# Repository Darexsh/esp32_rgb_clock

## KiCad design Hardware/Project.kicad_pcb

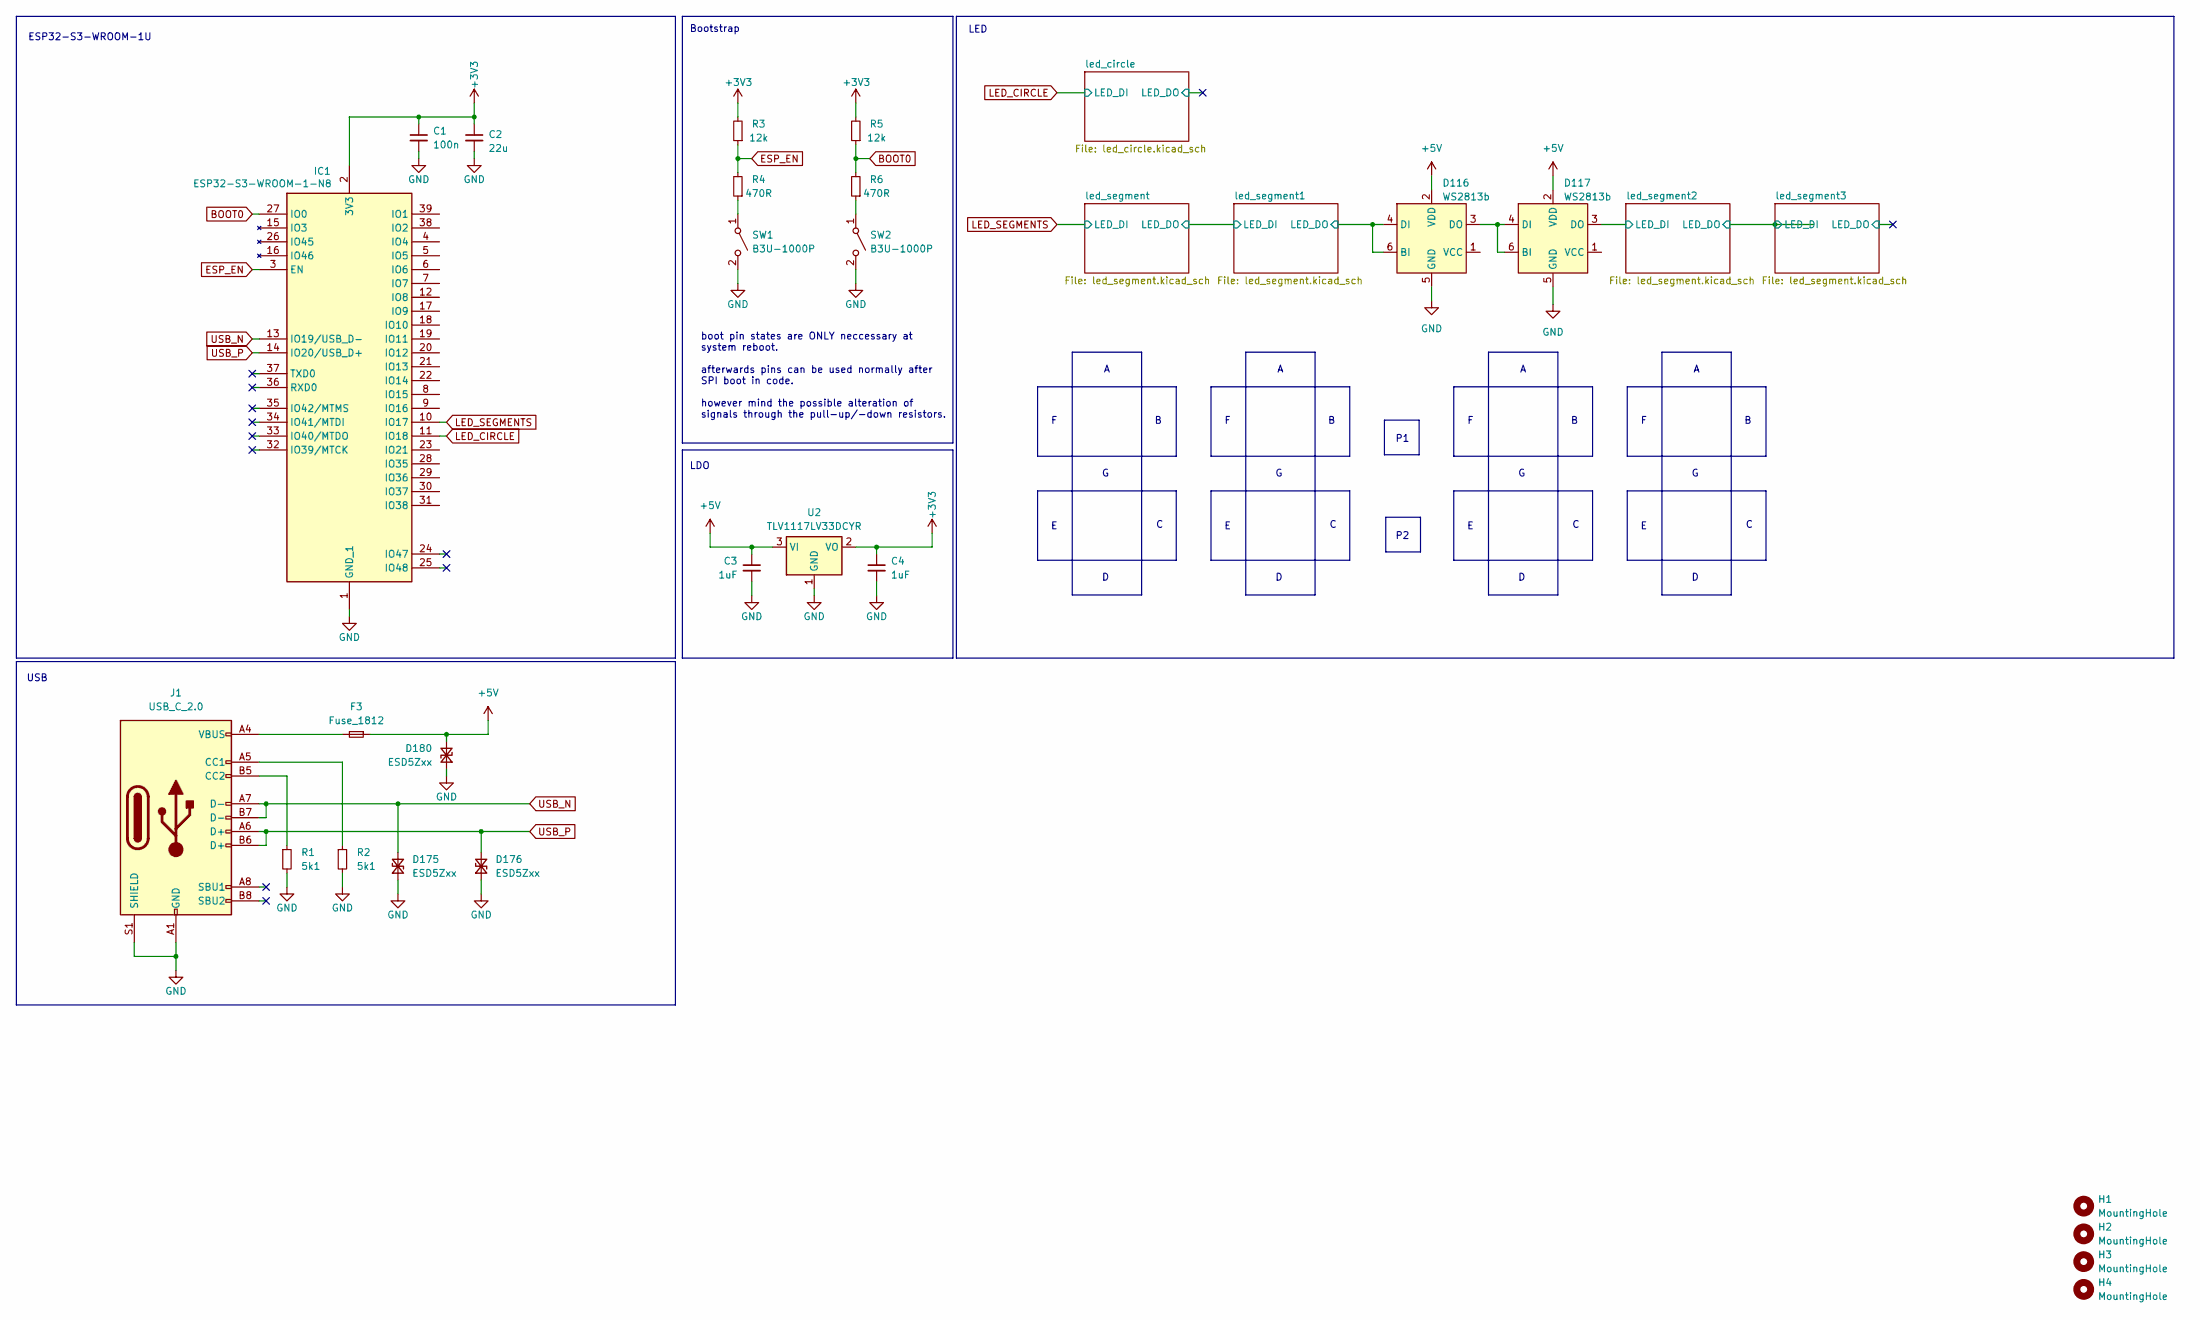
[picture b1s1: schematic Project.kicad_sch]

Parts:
C1: 100n; C_0603_1608Metric
C2: 22u; C_0603_1608Metric
C3, C4: 1uF; C_0603_1608Metric
D116, D117: WS2813b; LED_WS2812_PLCC6_5.0x5.0mm_P1.6mm
D175, D176, D180: ESD5Zxx; D_SOD-523
F3: Fuse_1812; Fuse_1812_4532Metric
H1, H2, H3, H4: MountingHole; MountingHole_3.2mm_M3
IC1: ESP32-S3-WROOM-1-N8; ESP32S3WROOM1N8R8
J1: USB_C_2.0; USB-C
R1, R2: 5k1; R_0603_1608Metric
R3, R5: 12k; R_0603_1608Metric
R4, R6: 470R; R_0603_1608Metric
SW1, SW2: B3U-1000P
U2: TLV1117LV33DCYR; SOT-223-3_TabPin2

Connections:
+3V3: C1.1, C2.1, C4.1, IC1.2 (3V3), R3.2, R5.2, U2.2 (VO)
+5V: C3.1, D116.2 (VDD), D117.2 (VDD), D180.2 (A2), F3.1, U2.3 (VI); also elsewhere on the board
/led_segment1/LED_DO: D116.4 (DI), D116.6 (BI); also elsewhere on the board
/led_segment2/LED_DI: D117.3 (DO); also elsewhere on the board
BOOT0: IC1.27 (IO0), R5.1, R6.2
ESP_EN: IC1.3 (EN), R3.1, R4.2
GND: C1.2, C2.2, C3.2, C4.2, D116.5 (GND), D117.5 (GND), D175.1 (A1), D176.1 (A1), D180.1 (A1), IC1.1 (GND_1), IC1.40 (GND_2), IC1.41 (GND_3), IC1.42 (GND_4), IC1.43 (GND_5), IC1.44 (GND_6), IC1.45 (GND_7), IC1.46 (GND_8), IC1.47 (GND_9), IC1.48 (GND_10), IC1.49 (GND_11), J1.A1 (GND), J1.A12 (GND), J1.S1 (SHIELD), R1.2, R2.2, SW1.2 (B), SW2.2 (B), U2.1 (GND); also elsewhere on the board
LED_CIRCLE: IC1.11 (IO18); also elsewhere on the board
LED_SEGMENTS: IC1.10 (IO17); also elsewhere on the board
unnamed: D116.3 (DO), D117.4 (DI), D117.6 (BI)
unnamed: F3.2, J1.A4 (VBUS), J1.A9 (VBUS)
unnamed: J1.A5 (CC1), R2.1
unnamed: J1.B5 (CC2), R1.1
unnamed: R4.1, SW1.1 (A)
unnamed: R6.1, SW2.1 (A)
USB_N: D175.2 (A2), IC1.13 (IO19/USB_D-), J1.A7 (D-), J1.B7 (D-)
USB_P: D176.2 (A2), IC1.14 (IO20/USB_D+), J1.A6 (D+), J1.B6 (D+)

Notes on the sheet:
LED
USB
LDO
Bootstrap
ESP32-S3-WROOM-1U
boot pin states are ONLY neccessary at system reboot. afterwards pins can be used normally after SPI boot in code. however mind the possible alteration of signals through the pull-up/-down resistors.

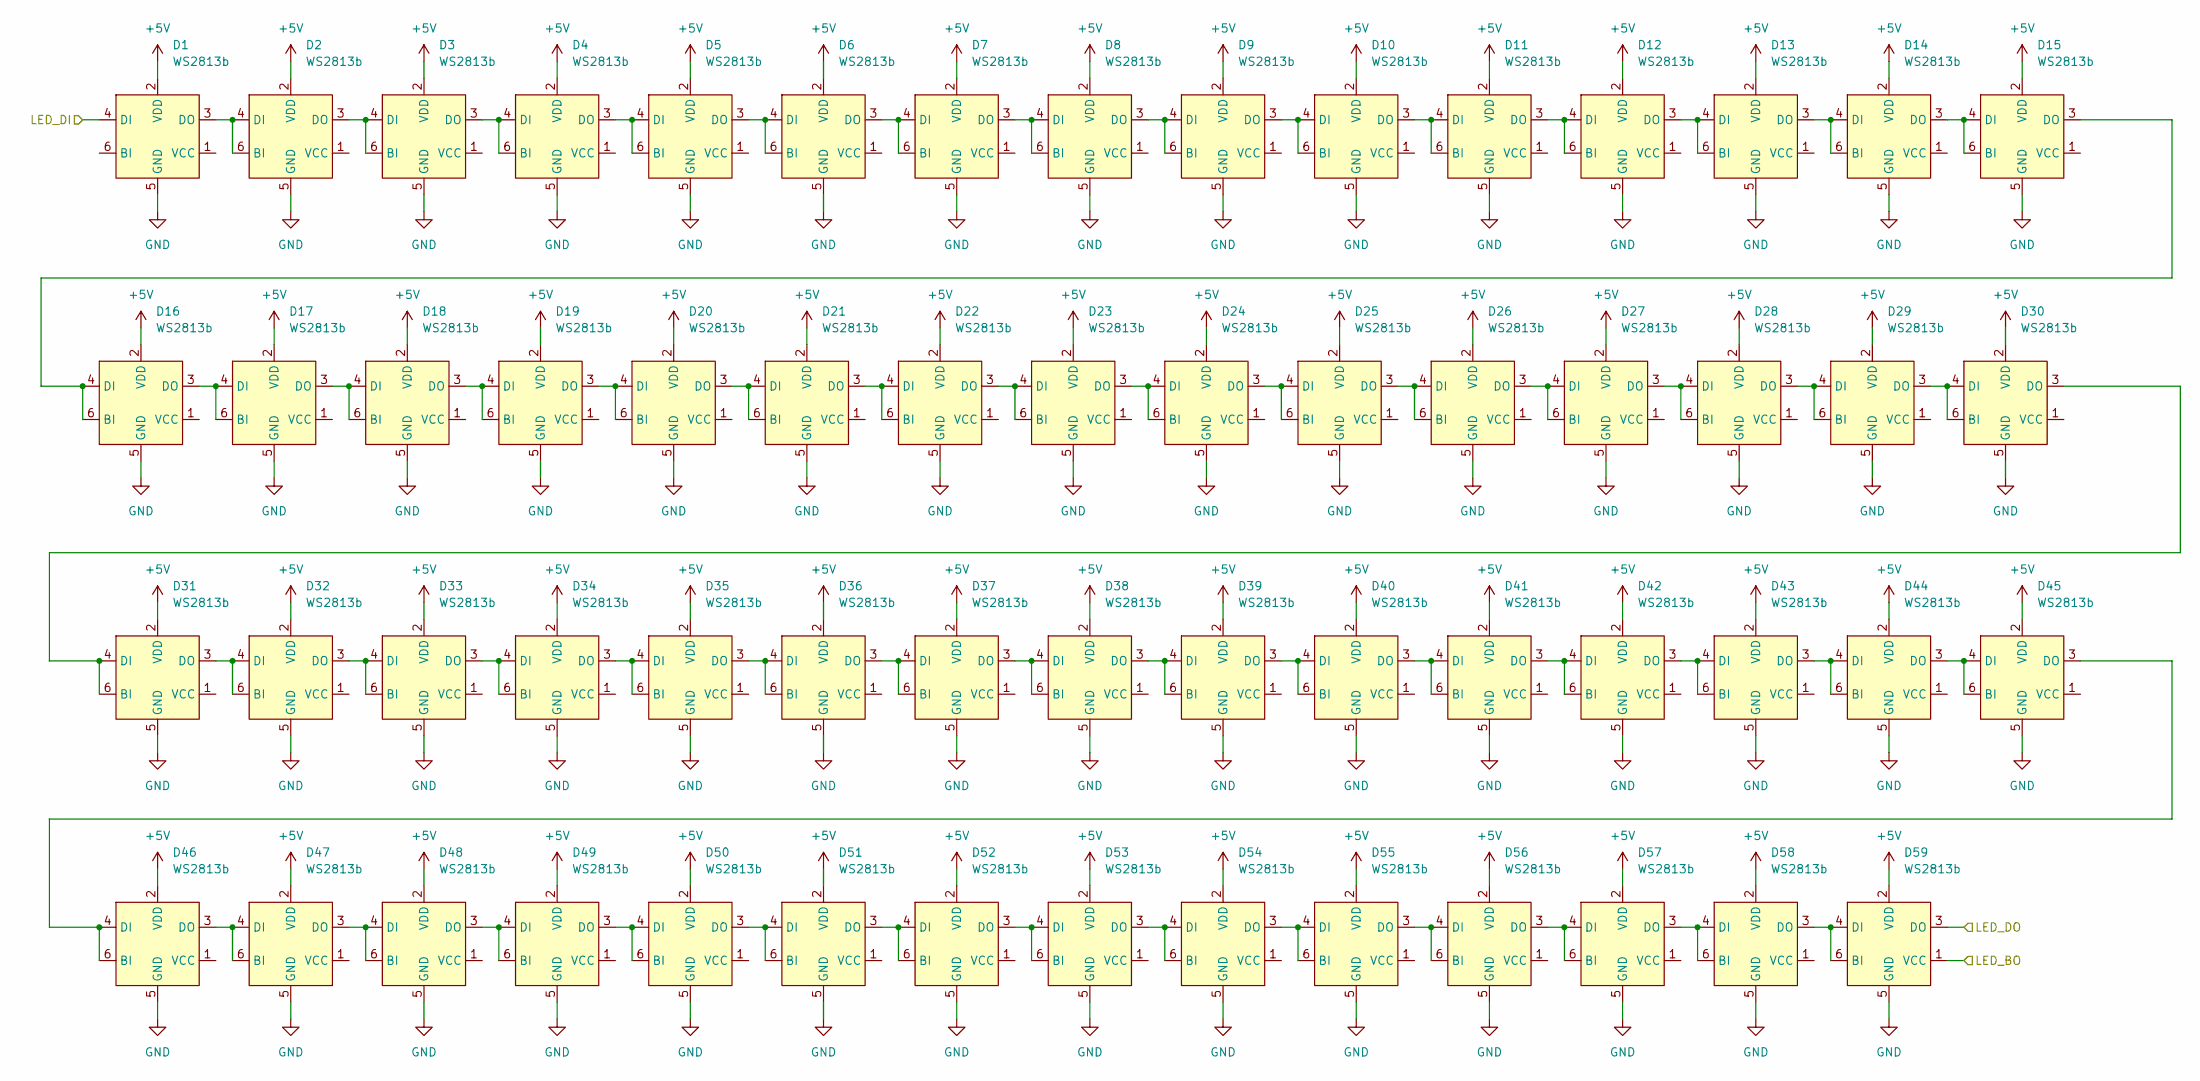
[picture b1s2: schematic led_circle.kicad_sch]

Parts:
D1, D2, D3, D4, D5, D6, D7, D8, D9, D10, D11, D12, D13, D14, D15, D16, D17, D18, D19, D20, D21, D22, D23, D24, D25, D26, D27, D28, D29, D30, D31, D32, D33, D34, D35, D36, D37, D38, D39, D40, D41, D42, D43, D44, D45, D46, D47, D48, D49, D50, D51, D52, D53, D54, D55, D56, D57, D58, D59: WS2813b; LED_WS2812_PLCC6_5.0x5.0mm_P1.6mm

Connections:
+5V: D1.2 (VDD), D2.2 (VDD), D3.2 (VDD), D4.2 (VDD), D5.2 (VDD), D6.2 (VDD), D7.2 (VDD), D8.2 (VDD), D9.2 (VDD), D10.2 (VDD), D11.2 (VDD), D12.2 (VDD), D13.2 (VDD), D14.2 (VDD), D15.2 (VDD), D16.2 (VDD), D17.2 (VDD), D18.2 (VDD), D19.2 (VDD), D20.2 (VDD), D21.2 (VDD), D22.2 (VDD), D23.2 (VDD), D24.2 (VDD), D25.2 (VDD), D26.2 (VDD), D27.2 (VDD), D28.2 (VDD), D29.2 (VDD), D30.2 (VDD), D31.2 (VDD), D32.2 (VDD), D33.2 (VDD), D34.2 (VDD), D35.2 (VDD), D36.2 (VDD), D37.2 (VDD), D38.2 (VDD), D39.2 (VDD), D40.2 (VDD), D41.2 (VDD), D42.2 (VDD), D43.2 (VDD), D44.2 (VDD), D45.2 (VDD), D46.2 (VDD), D47.2 (VDD), D48.2 (VDD), D49.2 (VDD), D50.2 (VDD), D51.2 (VDD), D52.2 (VDD), D53.2 (VDD), D54.2 (VDD), D55.2 (VDD), D56.2 (VDD), D57.2 (VDD), D58.2 (VDD), D59.2 (VDD); also elsewhere on the board
/led_circle/LED_BO: D59.1 (VCC)
/led_circle/LED_DO: D59.3 (DO)
GND: D1.5 (GND), D2.5 (GND), D3.5 (GND), D4.5 (GND), D5.5 (GND), D6.5 (GND), D7.5 (GND), D8.5 (GND), D9.5 (GND), D10.5 (GND), D11.5 (GND), D12.5 (GND), D13.5 (GND), D14.5 (GND), D15.5 (GND), D16.5 (GND), D17.5 (GND), D18.5 (GND), D19.5 (GND), D20.5 (GND), D21.5 (GND), D22.5 (GND), D23.5 (GND), D24.5 (GND), D25.5 (GND), D26.5 (GND), D27.5 (GND), D28.5 (GND), D29.5 (GND), D30.5 (GND), D31.5 (GND), D32.5 (GND), D33.5 (GND), D34.5 (GND), D35.5 (GND), D36.5 (GND), D37.5 (GND), D38.5 (GND), D39.5 (GND), D40.5 (GND), D41.5 (GND), D42.5 (GND), D43.5 (GND), D44.5 (GND), D45.5 (GND), D46.5 (GND), D47.5 (GND), D48.5 (GND), D49.5 (GND), D50.5 (GND), D51.5 (GND), D52.5 (GND), D53.5 (GND), D54.5 (GND), D55.5 (GND), D56.5 (GND), D57.5 (GND), D58.5 (GND), D59.5 (GND); also elsewhere on the board
LED_CIRCLE: D1.4 (DI); also elsewhere on the board
unnamed: D1.3 (DO), D2.4 (DI), D2.6 (BI)
unnamed: D2.3 (DO), D3.4 (DI), D3.6 (BI)
unnamed: D3.3 (DO), D4.4 (DI), D4.6 (BI)
unnamed: D4.3 (DO), D5.4 (DI), D5.6 (BI)
unnamed: D5.3 (DO), D6.4 (DI), D6.6 (BI)
unnamed: D6.3 (DO), D7.4 (DI), D7.6 (BI)
unnamed: D7.3 (DO), D8.4 (DI), D8.6 (BI)
unnamed: D8.3 (DO), D9.4 (DI), D9.6 (BI)
unnamed: D9.3 (DO), D10.4 (DI), D10.6 (BI)
unnamed: D10.3 (DO), D11.4 (DI), D11.6 (BI)
unnamed: D11.3 (DO), D12.4 (DI), D12.6 (BI)
unnamed: D12.3 (DO), D13.4 (DI), D13.6 (BI)
unnamed: D13.3 (DO), D14.4 (DI), D14.6 (BI)
unnamed: D14.3 (DO), D15.4 (DI), D15.6 (BI)
unnamed: D15.3 (DO), D16.4 (DI), D16.6 (BI)
unnamed: D16.3 (DO), D17.4 (DI), D17.6 (BI)
unnamed: D17.3 (DO), D18.4 (DI), D18.6 (BI)
unnamed: D18.3 (DO), D19.4 (DI), D19.6 (BI)
unnamed: D19.3 (DO), D20.4 (DI), D20.6 (BI)
unnamed: D20.3 (DO), D21.4 (DI), D21.6 (BI)
unnamed: D21.3 (DO), D22.4 (DI), D22.6 (BI)
unnamed: D22.3 (DO), D23.4 (DI), D23.6 (BI)
unnamed: D23.3 (DO), D24.4 (DI), D24.6 (BI)
unnamed: D24.3 (DO), D25.4 (DI), D25.6 (BI)
unnamed: D25.3 (DO), D26.4 (DI), D26.6 (BI)
unnamed: D26.3 (DO), D27.4 (DI), D27.6 (BI)
unnamed: D27.3 (DO), D28.4 (DI), D28.6 (BI)
unnamed: D28.3 (DO), D29.4 (DI), D29.6 (BI)
unnamed: D29.3 (DO), D30.4 (DI), D30.6 (BI)
unnamed: D30.3 (DO), D31.4 (DI), D31.6 (BI)
unnamed: D31.3 (DO), D32.4 (DI), D32.6 (BI)
unnamed: D32.3 (DO), D33.4 (DI), D33.6 (BI)
unnamed: D33.3 (DO), D34.4 (DI), D34.6 (BI)
unnamed: D34.3 (DO), D35.4 (DI), D35.6 (BI)
unnamed: D35.3 (DO), D36.4 (DI), D36.6 (BI)
unnamed: D36.3 (DO), D37.4 (DI), D37.6 (BI)
unnamed: D37.3 (DO), D38.4 (DI), D38.6 (BI)
unnamed: D38.3 (DO), D39.4 (DI), D39.6 (BI)
unnamed: D39.3 (DO), D40.4 (DI), D40.6 (BI)
unnamed: D40.3 (DO), D41.4 (DI), D41.6 (BI)
unnamed: D41.3 (DO), D42.4 (DI), D42.6 (BI)
unnamed: D42.3 (DO), D43.4 (DI), D43.6 (BI)
unnamed: D43.3 (DO), D44.4 (DI), D44.6 (BI)
unnamed: D44.3 (DO), D45.4 (DI), D45.6 (BI)
unnamed: D45.3 (DO), D46.4 (DI), D46.6 (BI)
unnamed: D46.3 (DO), D47.4 (DI), D47.6 (BI)
unnamed: D47.3 (DO), D48.4 (DI), D48.6 (BI)
unnamed: D48.3 (DO), D49.4 (DI), D49.6 (BI)
unnamed: D49.3 (DO), D50.4 (DI), D50.6 (BI)
unnamed: D50.3 (DO), D51.4 (DI), D51.6 (BI)
unnamed: D51.3 (DO), D52.4 (DI), D52.6 (BI)
unnamed: D52.3 (DO), D53.4 (DI), D53.6 (BI)
unnamed: D53.3 (DO), D54.4 (DI), D54.6 (BI)
unnamed: D54.3 (DO), D55.4 (DI), D55.6 (BI)
unnamed: D55.3 (DO), D56.4 (DI), D56.6 (BI)
unnamed: D56.3 (DO), D57.4 (DI), D57.6 (BI)
unnamed: D57.3 (DO), D58.4 (DI), D58.6 (BI)
unnamed: D58.3 (DO), D59.4 (DI), D59.6 (BI)

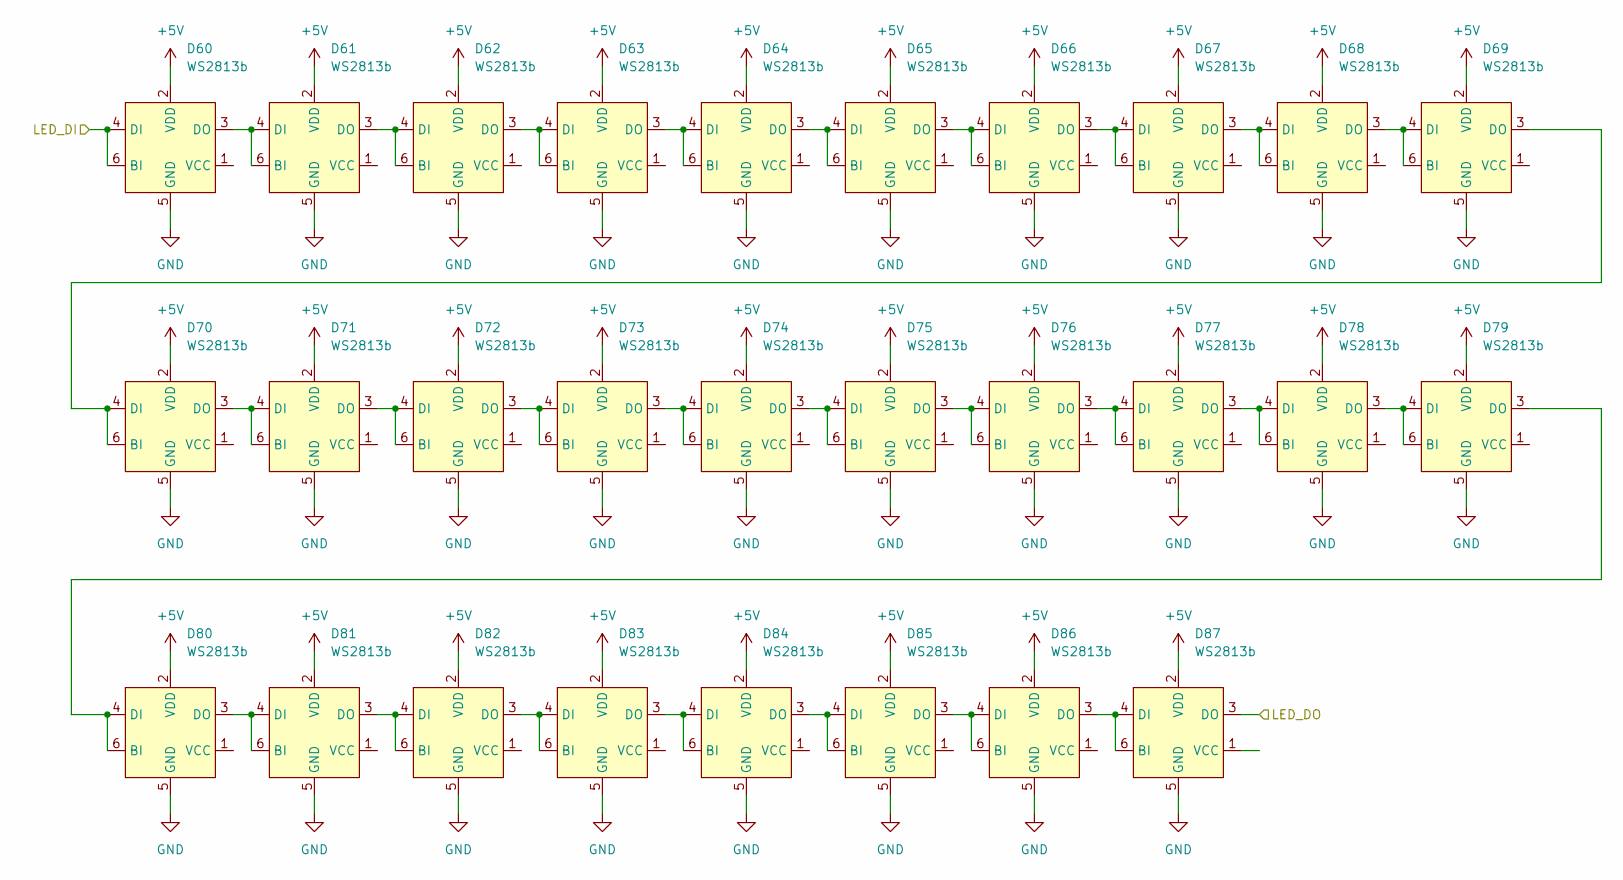
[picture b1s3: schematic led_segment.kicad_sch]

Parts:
D60, D61, D62, D63, D64, D65, D66, D67, D68, D69, D70, D71, D72, D73, D74, D75, D76, D77, D78, D79, D80, D81, D82, D83, D84, D85, D86, D87: WS2813b; LED_WS2812_PLCC6_5.0x5.0mm_P1.6mm

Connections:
+5V: D60.2 (VDD), D61.2 (VDD), D62.2 (VDD), D63.2 (VDD), D64.2 (VDD), D65.2 (VDD), D66.2 (VDD), D67.2 (VDD), D68.2 (VDD), D69.2 (VDD), D70.2 (VDD), D71.2 (VDD), D72.2 (VDD), D73.2 (VDD), D74.2 (VDD), D75.2 (VDD), D76.2 (VDD), D77.2 (VDD), D78.2 (VDD), D79.2 (VDD), D80.2 (VDD), D81.2 (VDD), D82.2 (VDD), D83.2 (VDD), D84.2 (VDD), D85.2 (VDD), D86.2 (VDD), D87.2 (VDD); also elsewhere on the board
/led_segment/LED_DO: D87.3 (DO); also elsewhere on the board
GND: D60.5 (GND), D61.5 (GND), D62.5 (GND), D63.5 (GND), D64.5 (GND), D65.5 (GND), D66.5 (GND), D67.5 (GND), D68.5 (GND), D69.5 (GND), D70.5 (GND), D71.5 (GND), D72.5 (GND), D73.5 (GND), D74.5 (GND), D75.5 (GND), D76.5 (GND), D77.5 (GND), D78.5 (GND), D79.5 (GND), D80.5 (GND), D81.5 (GND), D82.5 (GND), D83.5 (GND), D84.5 (GND), D85.5 (GND), D86.5 (GND), D87.5 (GND); also elsewhere on the board
LED_SEGMENTS: D60.4 (DI), D60.6 (BI); also elsewhere on the board
unnamed: D60.3 (DO), D61.4 (DI), D61.6 (BI)
unnamed: D61.3 (DO), D62.4 (DI), D62.6 (BI)
unnamed: D62.3 (DO), D63.4 (DI), D63.6 (BI)
unnamed: D63.3 (DO), D64.4 (DI), D64.6 (BI)
unnamed: D64.3 (DO), D65.4 (DI), D65.6 (BI)
unnamed: D65.3 (DO), D66.4 (DI), D66.6 (BI)
unnamed: D66.3 (DO), D67.4 (DI), D67.6 (BI)
unnamed: D67.3 (DO), D68.4 (DI), D68.6 (BI)
unnamed: D68.3 (DO), D69.4 (DI), D69.6 (BI)
unnamed: D69.3 (DO), D70.4 (DI), D70.6 (BI)
unnamed: D70.3 (DO), D71.4 (DI), D71.6 (BI)
unnamed: D71.3 (DO), D72.4 (DI), D72.6 (BI)
unnamed: D72.3 (DO), D73.4 (DI), D73.6 (BI)
unnamed: D73.3 (DO), D74.4 (DI), D74.6 (BI)
unnamed: D74.3 (DO), D75.4 (DI), D75.6 (BI)
unnamed: D75.3 (DO), D76.4 (DI), D76.6 (BI)
unnamed: D76.3 (DO), D77.4 (DI), D77.6 (BI)
unnamed: D77.3 (DO), D78.4 (DI), D78.6 (BI)
unnamed: D78.3 (DO), D79.4 (DI), D79.6 (BI)
unnamed: D79.3 (DO), D80.4 (DI), D80.6 (BI)
unnamed: D80.3 (DO), D81.4 (DI), D81.6 (BI)
unnamed: D81.3 (DO), D82.4 (DI), D82.6 (BI)
unnamed: D82.3 (DO), D83.4 (DI), D83.6 (BI)
unnamed: D83.3 (DO), D84.4 (DI), D84.6 (BI)
unnamed: D84.3 (DO), D85.4 (DI), D85.6 (BI)
unnamed: D85.3 (DO), D86.4 (DI), D86.6 (BI)
unnamed: D86.3 (DO), D87.4 (DI), D87.6 (BI)

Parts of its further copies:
D88, D89, D90, D91, D92, D93, D94, D95, D96, D97, D98, D99, D100, D101, D102, D103, D104, D105, D106, D107, D108, D109, D110, D111, D112, D113, D114, D115, D118, D119, D120, D121, D122, D123, D124, D125, D126, D127, D128, D129, D130, D131, D132, D133, D134, D135, D136, D137, D138, D139, D140, D141, D142, D143, D144, D145, D146, D147, D148, D149, D150, D151, D152, D153, D154, D155, D156, D157, D158, D159, D160, D161, D162, D163, D164, D165, D166, D167, D168, D169, D170, D171, D172, D173: WS2813b; LED_WS2812_PLCC6_5.0x5.0mm_P1.6mm

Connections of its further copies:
+5V: D88.2 (VDD), D89.2 (VDD), D90.2 (VDD), D91.2 (VDD), D92.2 (VDD), D93.2 (VDD), D94.2 (VDD), D95.2 (VDD), D96.2 (VDD), D97.2 (VDD), D98.2 (VDD), D99.2 (VDD), D100.2 (VDD), D101.2 (VDD), D102.2 (VDD), D103.2 (VDD), D104.2 (VDD), D105.2 (VDD), D106.2 (VDD), D107.2 (VDD), D108.2 (VDD), D109.2 (VDD), D110.2 (VDD), D111.2 (VDD), D112.2 (VDD), D113.2 (VDD), D114.2 (VDD), D115.2 (VDD), D118.2 (VDD), D119.2 (VDD), D120.2 (VDD), D121.2 (VDD), D122.2 (VDD), D123.2 (VDD), D124.2 (VDD), D125.2 (VDD), D126.2 (VDD), D127.2 (VDD), D128.2 (VDD), D129.2 (VDD), D130.2 (VDD), D131.2 (VDD), D132.2 (VDD), D133.2 (VDD), D134.2 (VDD), D135.2 (VDD), D136.2 (VDD), D137.2 (VDD), D138.2 (VDD), D139.2 (VDD), D140.2 (VDD), D141.2 (VDD), D142.2 (VDD), D143.2 (VDD), D144.2 (VDD), D145.2 (VDD), D146.2 (VDD), D147.2 (VDD), D148.2 (VDD), D149.2 (VDD), D150.2 (VDD), D151.2 (VDD), D152.2 (VDD), D153.2 (VDD), D154.2 (VDD), D155.2 (VDD), D156.2 (VDD), D157.2 (VDD), D158.2 (VDD), D159.2 (VDD), D160.2 (VDD), D161.2 (VDD), D162.2 (VDD), D163.2 (VDD), D164.2 (VDD), D165.2 (VDD), D166.2 (VDD), D167.2 (VDD), D168.2 (VDD), D169.2 (VDD), D170.2 (VDD), D171.2 (VDD), D172.2 (VDD), D173.2 (VDD); also elsewhere on the board
/led_segment1/LED_DO: D115.3 (DO); also elsewhere on the board
/led_segment2/LED_DI: D118.4 (DI), D118.6 (BI); also elsewhere on the board
/led_segment2/LED_DO: D145.3 (DO), D146.4 (DI), D146.6 (BI)
/led_segment3/LED_DO: D173.3 (DO)
/led_segment/LED_DO: D88.4 (DI), D88.6 (BI); also elsewhere on the board
GND: D88.5 (GND), D89.5 (GND), D90.5 (GND), D91.5 (GND), D92.5 (GND), D93.5 (GND), D94.5 (GND), D95.5 (GND), D96.5 (GND), D97.5 (GND), D98.5 (GND), D99.5 (GND), D100.5 (GND), D101.5 (GND), D102.5 (GND), D103.5 (GND), D104.5 (GND), D105.5 (GND), D106.5 (GND), D107.5 (GND), D108.5 (GND), D109.5 (GND), D110.5 (GND), D111.5 (GND), D112.5 (GND), D113.5 (GND), D114.5 (GND), D115.5 (GND), D118.5 (GND), D119.5 (GND), D120.5 (GND), D121.5 (GND), D122.5 (GND), D123.5 (GND), D124.5 (GND), D125.5 (GND), D126.5 (GND), D127.5 (GND), D128.5 (GND), D129.5 (GND), D130.5 (GND), D131.5 (GND), D132.5 (GND), D133.5 (GND), D134.5 (GND), D135.5 (GND), D136.5 (GND), D137.5 (GND), D138.5 (GND), D139.5 (GND), D140.5 (GND), D141.5 (GND), D142.5 (GND), D143.5 (GND), D144.5 (GND), D145.5 (GND), D146.5 (GND), D147.5 (GND), D148.5 (GND), D149.5 (GND), D150.5 (GND), D151.5 (GND), D152.5 (GND), D153.5 (GND), D154.5 (GND), D155.5 (GND), D156.5 (GND), D157.5 (GND), D158.5 (GND), D159.5 (GND), D160.5 (GND), D161.5 (GND), D162.5 (GND), D163.5 (GND), D164.5 (GND), D165.5 (GND), D166.5 (GND), D167.5 (GND), D168.5 (GND), D169.5 (GND), D170.5 (GND), D171.5 (GND), D172.5 (GND), D173.5 (GND); also elsewhere on the board
unnamed: D88.3 (DO), D89.4 (DI), D89.6 (BI)
unnamed: D89.3 (DO), D90.4 (DI), D90.6 (BI)
unnamed: D90.3 (DO), D91.4 (DI), D91.6 (BI)
unnamed: D91.3 (DO), D92.4 (DI), D92.6 (BI)
unnamed: D92.3 (DO), D93.4 (DI), D93.6 (BI)
unnamed: D93.3 (DO), D94.4 (DI), D94.6 (BI)
unnamed: D94.3 (DO), D95.4 (DI), D95.6 (BI)
unnamed: D95.3 (DO), D96.4 (DI), D96.6 (BI)
unnamed: D96.3 (DO), D97.4 (DI), D97.6 (BI)
unnamed: D97.3 (DO), D98.4 (DI), D98.6 (BI)
unnamed: D98.3 (DO), D99.4 (DI), D99.6 (BI)
unnamed: D99.3 (DO), D100.4 (DI), D100.6 (BI)
unnamed: D100.3 (DO), D101.4 (DI), D101.6 (BI)
unnamed: D101.3 (DO), D102.4 (DI), D102.6 (BI)
unnamed: D102.3 (DO), D103.4 (DI), D103.6 (BI)
unnamed: D103.3 (DO), D104.4 (DI), D104.6 (BI)
unnamed: D104.3 (DO), D105.4 (DI), D105.6 (BI)
unnamed: D105.3 (DO), D106.4 (DI), D106.6 (BI)
unnamed: D106.3 (DO), D107.4 (DI), D107.6 (BI)
unnamed: D107.3 (DO), D108.4 (DI), D108.6 (BI)
unnamed: D108.3 (DO), D109.4 (DI), D109.6 (BI)
unnamed: D109.3 (DO), D110.4 (DI), D110.6 (BI)
unnamed: D110.3 (DO), D111.4 (DI), D111.6 (BI)
unnamed: D111.3 (DO), D112.4 (DI), D112.6 (BI)
unnamed: D112.3 (DO), D113.4 (DI), D113.6 (BI)
unnamed: D113.3 (DO), D114.4 (DI), D114.6 (BI)
unnamed: D114.3 (DO), D115.4 (DI), D115.6 (BI)
unnamed: D118.3 (DO), D119.4 (DI), D119.6 (BI)
unnamed: D119.3 (DO), D120.4 (DI), D120.6 (BI)
unnamed: D120.3 (DO), D121.4 (DI), D121.6 (BI)
unnamed: D121.3 (DO), D122.4 (DI), D122.6 (BI)
unnamed: D122.3 (DO), D123.4 (DI), D123.6 (BI)
unnamed: D123.3 (DO), D124.4 (DI), D124.6 (BI)
unnamed: D124.3 (DO), D125.4 (DI), D125.6 (BI)
unnamed: D125.3 (DO), D126.4 (DI), D126.6 (BI)
unnamed: D126.3 (DO), D127.4 (DI), D127.6 (BI)
unnamed: D127.3 (DO), D128.4 (DI), D128.6 (BI)
unnamed: D128.3 (DO), D129.4 (DI), D129.6 (BI)
unnamed: D129.3 (DO), D130.4 (DI), D130.6 (BI)
unnamed: D130.3 (DO), D131.4 (DI), D131.6 (BI)
unnamed: D131.3 (DO), D132.4 (DI), D132.6 (BI)
unnamed: D132.3 (DO), D133.4 (DI), D133.6 (BI)
unnamed: D133.3 (DO), D134.4 (DI), D134.6 (BI)
unnamed: D134.3 (DO), D135.4 (DI), D135.6 (BI)
unnamed: D135.3 (DO), D136.4 (DI), D136.6 (BI)
unnamed: D136.3 (DO), D137.4 (DI), D137.6 (BI)
unnamed: D137.3 (DO), D138.4 (DI), D138.6 (BI)
unnamed: D138.3 (DO), D139.4 (DI), D139.6 (BI)
unnamed: D139.3 (DO), D140.4 (DI), D140.6 (BI)
unnamed: D140.3 (DO), D141.4 (DI), D141.6 (BI)
unnamed: D141.3 (DO), D142.4 (DI), D142.6 (BI)
unnamed: D142.3 (DO), D143.4 (DI), D143.6 (BI)
unnamed: D143.3 (DO), D144.4 (DI), D144.6 (BI)
unnamed: D144.3 (DO), D145.4 (DI), D145.6 (BI)
unnamed: D146.3 (DO), D147.4 (DI), D147.6 (BI)
unnamed: D147.3 (DO), D148.4 (DI), D148.6 (BI)
unnamed: D148.3 (DO), D149.4 (DI), D149.6 (BI)
unnamed: D149.3 (DO), D150.4 (DI), D150.6 (BI)
unnamed: D150.3 (DO), D151.4 (DI), D151.6 (BI)
unnamed: D151.3 (DO), D152.4 (DI), D152.6 (BI)
unnamed: D152.3 (DO), D153.4 (DI), D153.6 (BI)
unnamed: D153.3 (DO), D154.4 (DI), D154.6 (BI)
unnamed: D154.3 (DO), D155.4 (DI), D155.6 (BI)
unnamed: D155.3 (DO), D156.4 (DI), D156.6 (BI)
unnamed: D156.3 (DO), D157.4 (DI), D157.6 (BI)
unnamed: D157.3 (DO), D158.4 (DI), D158.6 (BI)
unnamed: D158.3 (DO), D159.4 (DI), D159.6 (BI)
unnamed: D159.3 (DO), D160.4 (DI), D160.6 (BI)
unnamed: D160.3 (DO), D161.4 (DI), D161.6 (BI)
unnamed: D161.3 (DO), D162.4 (DI), D162.6 (BI)
unnamed: D162.3 (DO), D163.4 (DI), D163.6 (BI)
unnamed: D163.3 (DO), D164.4 (DI), D164.6 (BI)
unnamed: D164.3 (DO), D165.4 (DI), D165.6 (BI)
unnamed: D165.3 (DO), D166.4 (DI), D166.6 (BI)
unnamed: D166.3 (DO), D167.4 (DI), D167.6 (BI)
unnamed: D167.3 (DO), D168.4 (DI), D168.6 (BI)
unnamed: D168.3 (DO), D169.4 (DI), D169.6 (BI)
unnamed: D169.3 (DO), D170.4 (DI), D170.6 (BI)
unnamed: D170.3 (DO), D171.4 (DI), D171.6 (BI)
unnamed: D171.3 (DO), D172.4 (DI), D172.6 (BI)
unnamed: D172.3 (DO), D173.4 (DI), D173.6 (BI)

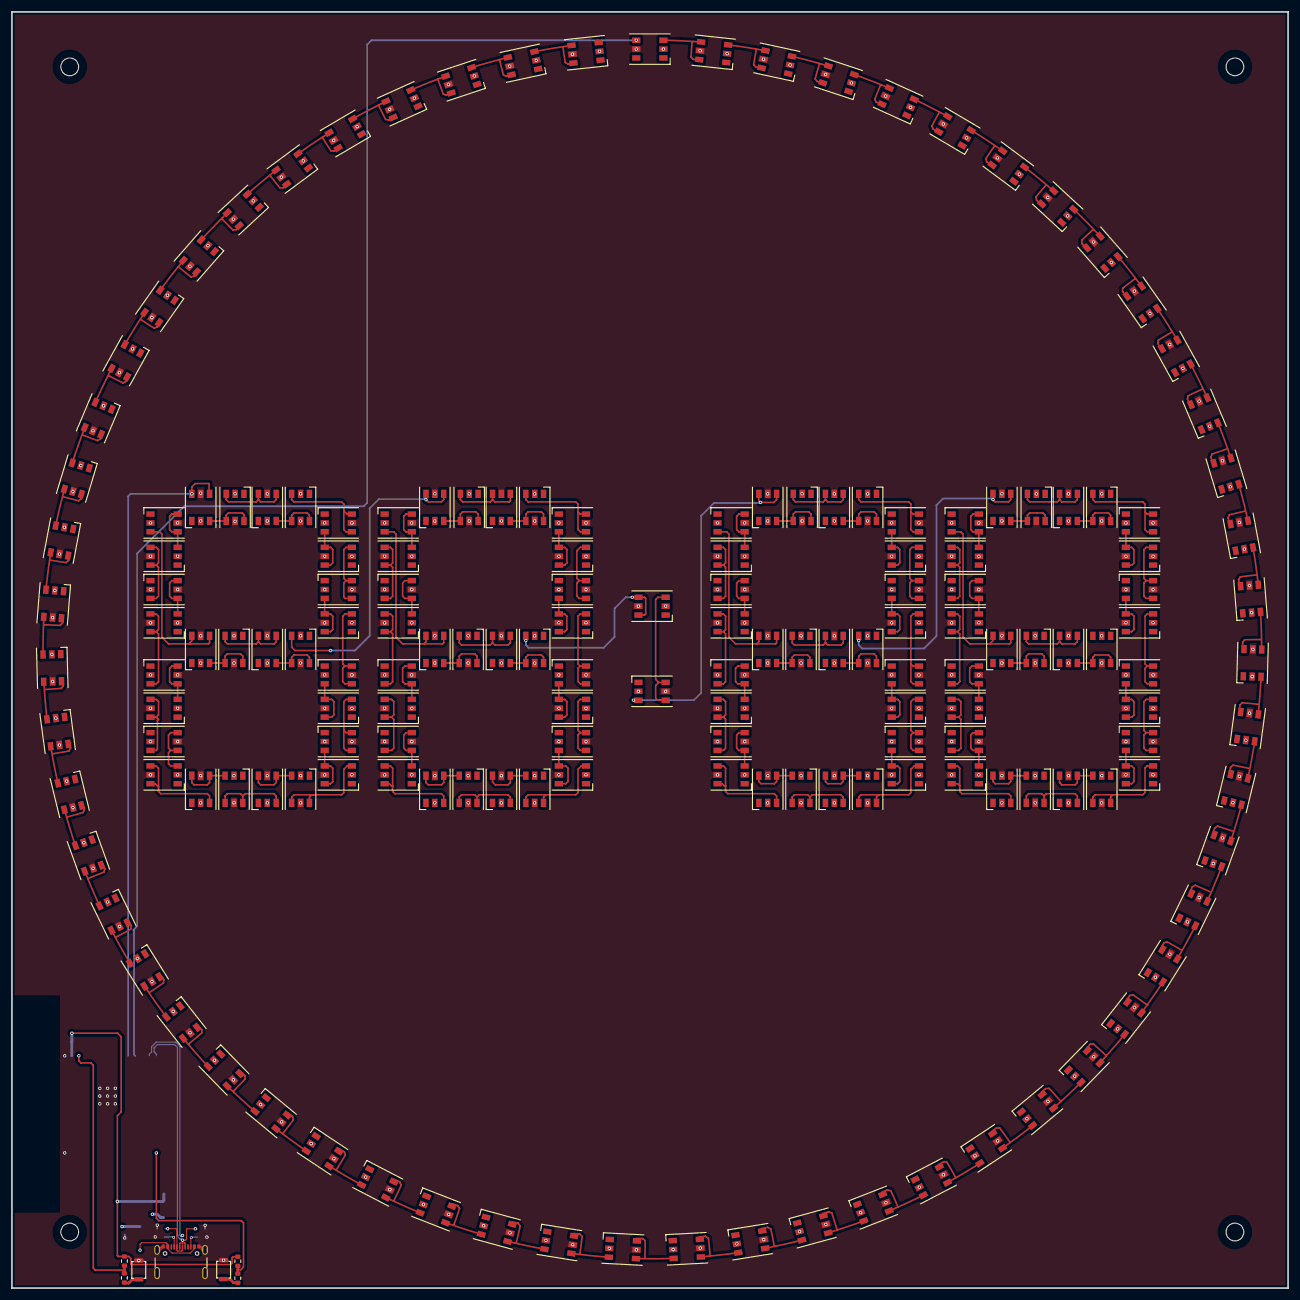
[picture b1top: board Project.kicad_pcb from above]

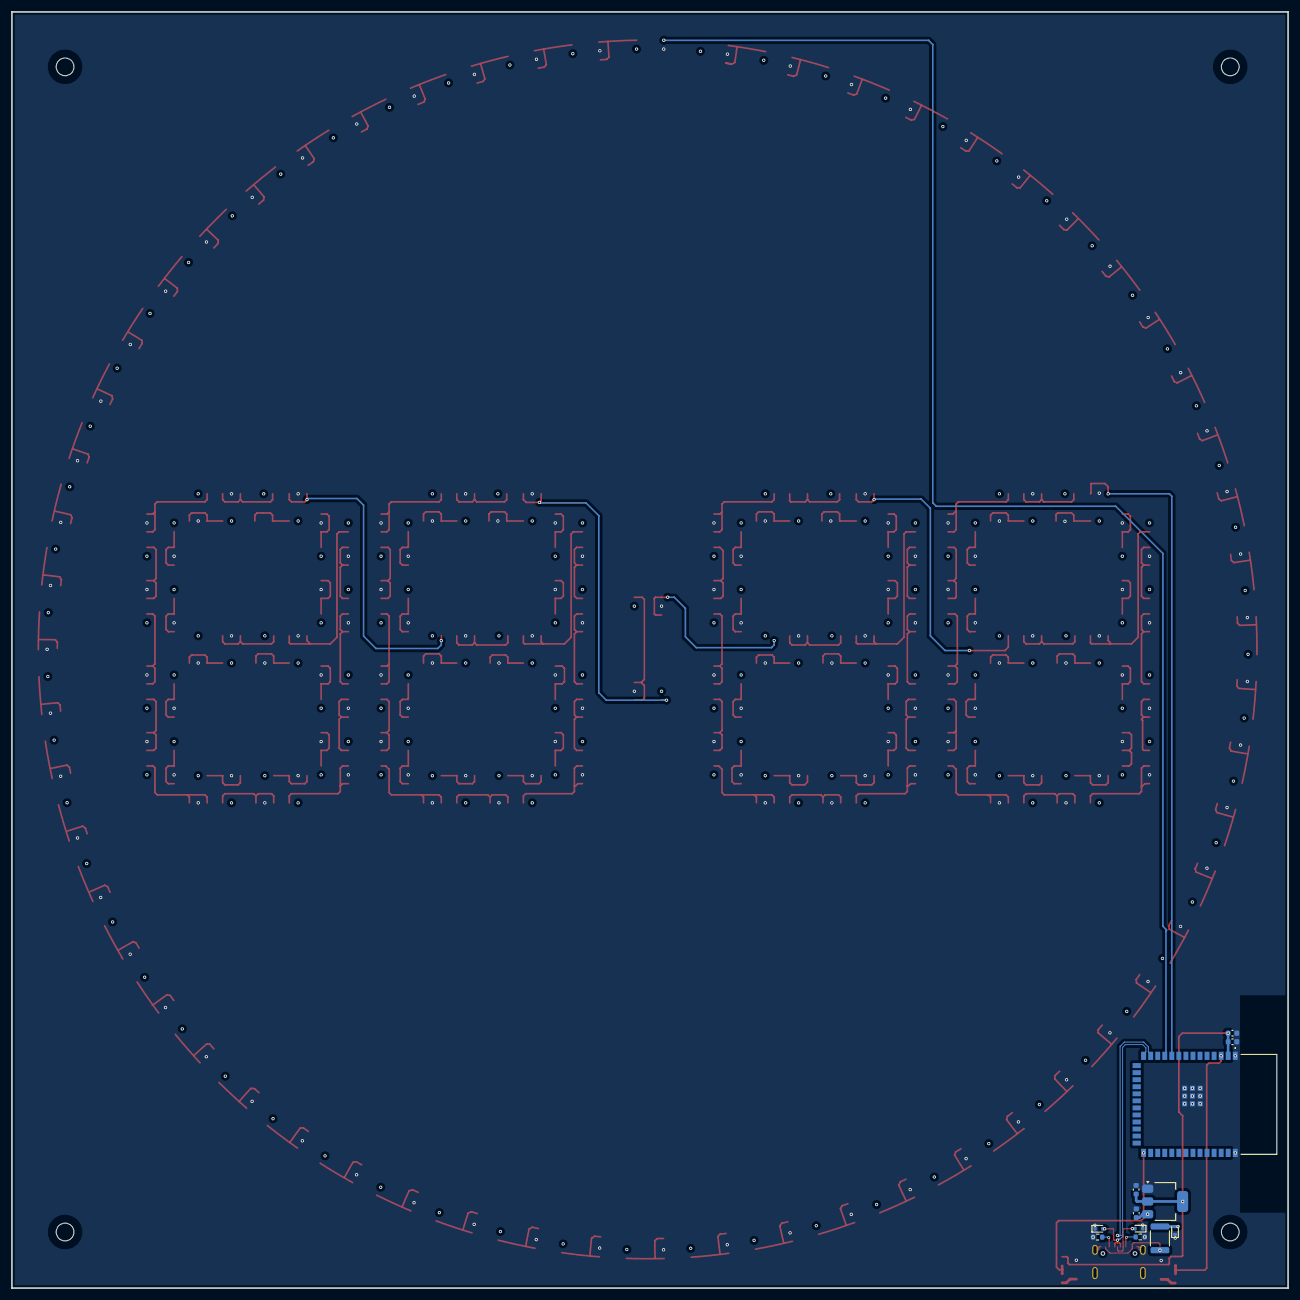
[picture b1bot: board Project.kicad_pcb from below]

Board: 4 copper layers, 230.0 x 230.0 mm, 196 parts (12 on the bottom side), 185 nets.

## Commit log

2025-07-01 Added ESP32-WROOM
2025-07-03 Finished layout
